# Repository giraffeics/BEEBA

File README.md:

# BEEBA

An 8-bit computer built using 7400 Series discrete logic chips.

## Repository Layout

The "CAD" folder contains all design files for the printed circuit boards. These are KiCAD documents.
The "Assembler" folder contains the C++ source code for the assembler, as well as the list of register names and some programs written in BEEBA assembly language. The assembler can be compiled with MinGW on Windows, and has not been tested on other compilers or operating systems.

## Assembly Language

Assembly language programs can be in any plain-text file format. The language is not case-sensitive. Each instruction copies eight bits of data from one register location to another. A line of code can follow one of three formats:

### COPY [read location] TO [write location]

Reads one byte of data from the register specified by [read location], writes data to the register specified by [write location].

### SET [write location] TO [data]

Writes a byte of data specified by [data] to the register specified by [write location]. [data] can be a two-digit hexadecimal number or a marker.

### MARK [marker name]

Marks the instruction position that corresponds to the following line of code. This does not represent an actual instruction. [marker name] can be referenced by SET instructions before or after the location of the marker, using a colon to specify which byte of the marker's location to use. This ranges from 0 (least significant) to 2 (most significant).

For all of these, any text after the last parameter will be ignored. However, it must be separated by a space or tab from the last parameter.

Register names are listed in REGISTER_NAMES.txt. The assembler uses this file to convert names to addresses while compiling programs.

## Using The Assembler

To use the assembler, simply drag assembly source files onto the compiled executable.

As BEEBA uses two physical ROM chips to store 16-bit-wide instructions, the assembler will output two .bin files. One of these is loaded onto the ROM chip on the left, the other is loaded onto the ROM chip on the right. They are named accordingly.

## Known Issues

When writing a constant to a register, the value will be corrupted unless the same data is sent to another register in the next instruction. The current workaround is to send data to NULL, which is an unused register.

The NES controller interface board cannot read the state of the A button. Pannenkoek2012 would love this.

The "Basic IO Board"'s input does not work at all. This was caused by oversights during the transition from TTL to CMOS. Output is still fully functional.

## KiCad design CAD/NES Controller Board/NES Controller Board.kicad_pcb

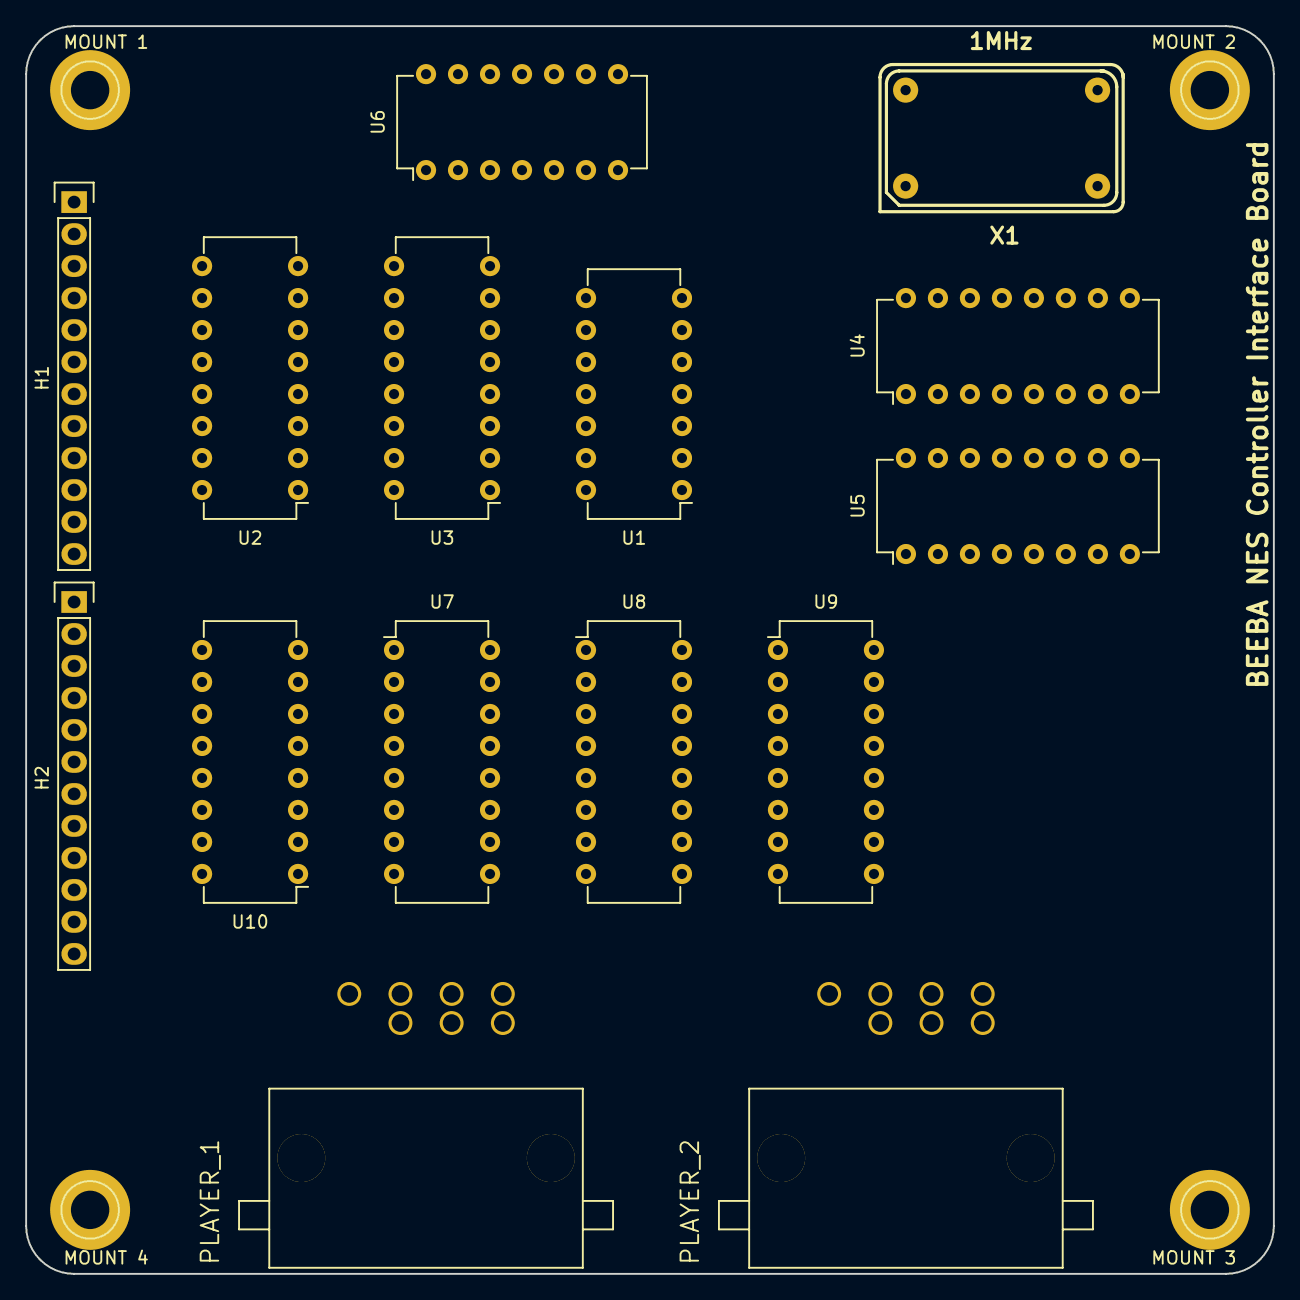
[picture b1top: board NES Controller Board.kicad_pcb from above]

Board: 2 copper layers, 99.1 x 99.1 mm, 19 parts (0 on the bottom side), 42 nets, no tracks yet.

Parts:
H1, H2: CONN_01X12; Socket_Strip_Straight_1x12
MOUNT 1, MOUNT 2, MOUNT 3, MOUNT 4: 1pin
PLAYER_1, PLAYER_2: NES_Controller_Port; NES_Controller_Port_RA
U1: 74LS04; DIP-14_W7.62mm
U2, U3: 74LS595; DIP-16_W7.62mm
U4, U7, U8: 74LS193; DIP-16_W7.62mm
U5, U9: 74LS85; DIP-16_W7.62mm
U6: 74LS08; DIP-14_W7.62mm
U10: 74LS138; DIP-16_W7.62mm
X1: 1MHz; XO-14S

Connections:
CNT0: U1.1, U6.2, U7.3, U9.10
CNT1: U1.5, U7.2, U9.12
CNT2: U7.6, U9.13
CNT4: U1.3, U6.9, U8.3, U9.15
DATA0: H1.10, U2.15, U3.15
DATA1: H1.9, U2.1, U3.1
DATA2: H1.8, U2.2, U3.2
DATA3: H1.7, U2.3, U3.3
DATA4: H1.6, U2.4, U3.4
DATA5: H1.5, U2.5, U3.5
DATA6: H1.4, U2.6, U3.6
DATA7: H1.3, U2.7, U3.7
GND: PLAYER_1.1, PLAYER_2.1, U1.7, U2.8, U3.8, U4.8, U5.2, U5.4, U5.8, U5.10, U5.15, U6.7, U7.8, U8.8, U9.2, U9.4, U9.8, U9.14, U10.8, X1.7
LATCH: PLAYER_1.3, PLAYER_2.3, U2.12, U3.12, U6.8
NCNT4: U1.4, U6.1, U6.5
unnamed: PLAYER_1.2, PLAYER_2.2, U6.6
unnamed: U1.2, U6.4
unnamed: U1.6, U6.10
unnamed: U1.8, U10.4
unnamed: U1.10, U2.14
unnamed: U1.12, U3.14
unnamed: U2.11, U3.11, U6.3
unnamed: U4.2, U5.14
unnamed: U4.3, U5.1
unnamed: U4.5, X1.8
unnamed: U4.6, U5.11
unnamed: U4.7, U5.9
unnamed: U4.14, U5.6, U7.5
unnamed: U7.12, U8.5
unnamed: U7.13, U8.4
unnamed: U7.14, U8.14, U9.6
P1_DATA: PLAYER_1.4, U1.11
P2_DATA: PLAYER_2.4, U1.13
READ0: H2.4, U10.1
READ1: H2.3, U10.2
READ2: H2.2, U10.3
READ3: H2.1, U1.9
READ4: H1.12, U10.5
READ5: H1.11, U10.6
RS43: U2.13, U10.12
RS44: U3.13, U10.11
VCC: H1.1, PLAYER_1.7, PLAYER_2.7, U1.14, U2.10, U2.16, U3.10, U3.16, U4.4, U4.11, U4.16, U5.3, U5.12, U5.13, U5.16, U6.14, U7.4, U7.11, U7.16, U8.11, U8.16, U9.1, U9.3, U9.9, U9.11, U9.16, U10.16, X1.14

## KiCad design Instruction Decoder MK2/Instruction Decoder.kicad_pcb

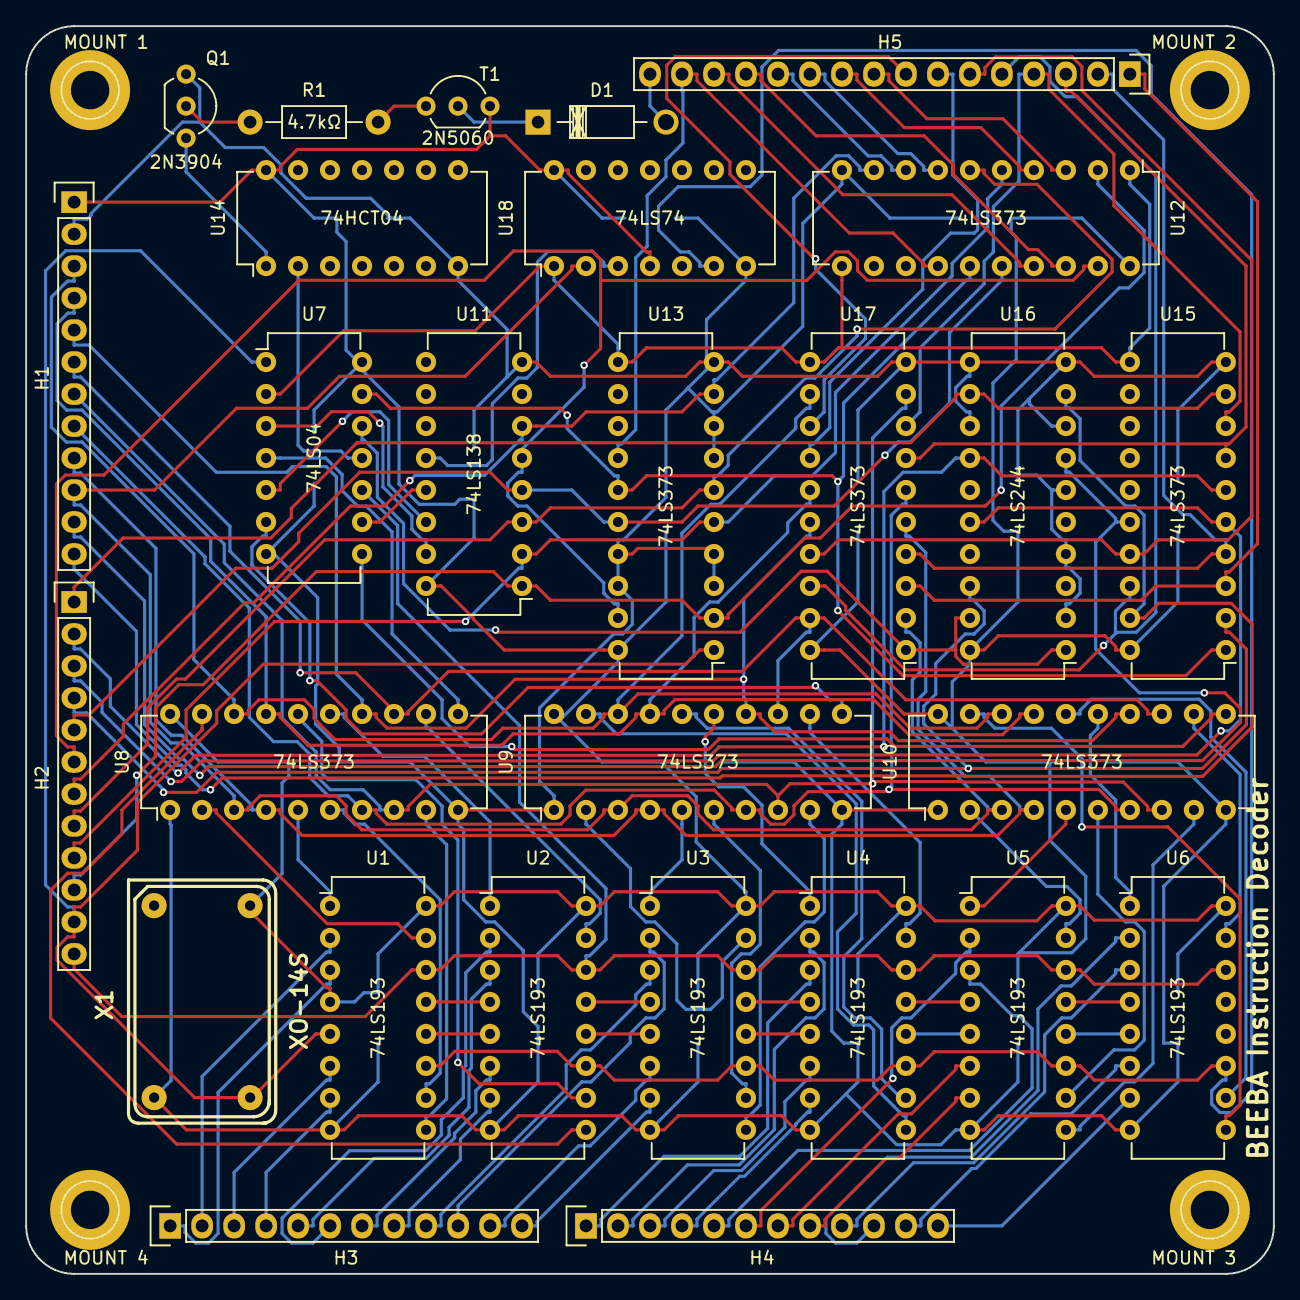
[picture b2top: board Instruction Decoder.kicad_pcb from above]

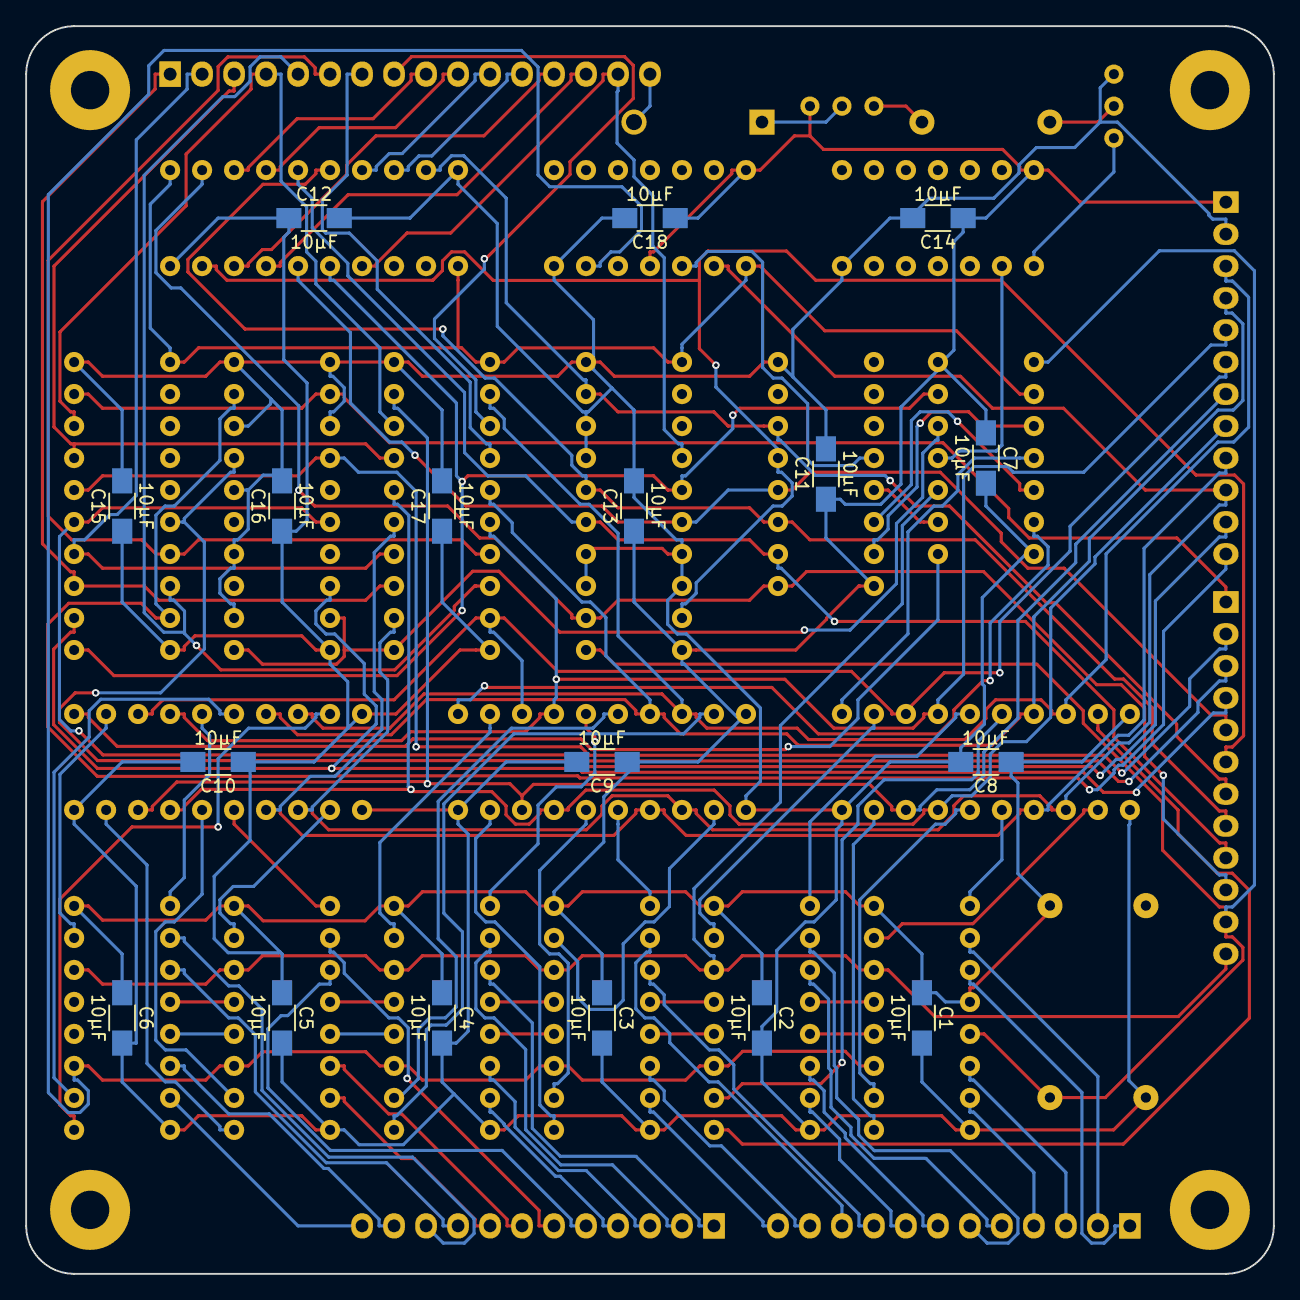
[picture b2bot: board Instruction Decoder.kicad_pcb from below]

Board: 2 copper layers, 99.1 x 99.1 mm, 50 parts (18 on the bottom side), 114 nets.

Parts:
C1, C2, C3, C4, C5, C6, C7, C8, C9, C10, C11, C12, C13, C14, C15, C16, C17, C18: 10µF; C_1206_HandSoldering
D1: D; Diode_DO-41_SOD81_Horizontal_RM10
H1, H2, H3, H4: CONN_01X12; Socket_Strip_Straight_1x12
H5: CONN_01X16; Socket_Strip_Straight_1x16
MOUNT 1, MOUNT 2, MOUNT 3, MOUNT 4: 1pin
Q1: 2N3904; TO-92_Inline_Wide
R1: 4.7kΩ; Resistor_Horizontal_RM10mm
T1: 2N5060; TO-92_Inline_Wide
U1, U2, U3, U4, U5, U6: 74LS193; DIP-16_W7.62mm
U7: 74LS04; DIP-14_W7.62mm
U8, U9, U10, U12, U13, U15, U17: 74LS373; DIP-20_W7.62mm
U11: 74LS138; DIP-16_W7.62mm
U14: 74HCT04; DIP-14_W7.62mm
U16: 74LS244; DIP-20_W7.62mm
U18: 74LS74; DIP-14_W7.62mm
X1: XO-14S

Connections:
CLOCK: H2.11, U1.5, U7.1, U13.1, X1.8
DATA0: H1.10, U8.3, U9.3, U10.3, U17.2, U18.2
DATA1: H1.9, U8.4, U9.4, U10.4, U17.5
DATA2: H1.8, U8.7, U9.7, U10.7, U17.6
DATA3: H1.7, U8.8, U9.8, U10.8, U17.9
DATA4: H1.6, U8.13, U9.13, U10.13, U17.19
DATA5: H1.5, U8.14, U9.14, U10.14, U17.16
DATA6: H1.4, U8.17, U9.17, U10.17, U17.15
DATA7: H1.3, U8.18, U9.18, U10.18, U17.12
GND: C1.2, C2.2, C3.2, C4.2, C5.2, C6.2, C7.2, C8.2, C9.2, C10.2, C11.2, C12.2, C13.2, C14.2, C15.2, C16.2, C17.2, C18.2, H1.2, Q1.1, U1.8, U2.8, U3.8, U4.8, U5.8, U6.8, U7.7, U8.1, U8.10, U9.1, U9.10, U10.1, U10.10, U11.8, U12.10, U13.3, U13.4, U13.7, U13.8, U13.10, U13.17, U13.18, U14.7, U15.10, U16.2, U16.4, U16.6, U16.8, U16.10, U16.11, U16.13, U17.10, U18.7, X1.7
II00: H5.1, U15.3, U17.3
II01: H5.2, U15.4, U17.4
II02: H5.3, U15.7, U17.7
II03: H5.4, U15.8, U17.8
II04: H5.5, U15.18, U17.18
II05: H5.6, U15.17, U17.17
II06: H5.7, U17.14
II07: H5.8, U17.13
II08: H5.9, U12.3
II09: H5.10, U12.4
II10: H5.11, U12.7
II11: H5.12, U12.8
II12: H5.13, U12.18
II13: H5.14, U12.17
II14: H5.15, U12.14, U13.14
II15: D1.2, H5.16
IL14: U7.13, U12.15, U13.15, U15.1
LOADP: U1.11, U2.11, U3.11, U4.11, U5.11, U6.11, U18.6
NCLOCK: U7.2, U12.1, U12.11, U13.11, U15.11, U17.11, U18.1
unnamed: D1.1, T1.G
unnamed: Q1.2, R1.2
unnamed: Q1.3, U14.1
unnamed: R1.1, T1.K
unnamed: U1.12, U2.5
unnamed: U1.13, U2.4
unnamed: U2.12, U3.5
unnamed: U2.13, U3.4
unnamed: U3.12, U4.5
unnamed: U3.13, U4.4
unnamed: U5.12, U6.5
unnamed: U5.13, U6.4
unnamed: U7.4, U8.11
unnamed: U7.6, U9.11
unnamed: U7.8, U10.11
unnamed: U7.11, U14.2
unnamed: U7.12, U16.1, U16.19, U17.1
PI00: U1.15, U8.2
PI01: U1.1, U8.5
PI02: U1.10, U8.6
PI03: U1.9, U8.9
PI04: U2.15, U8.12
PI05: U2.1, U8.15
PI06: U2.10, U8.16
PI07: U2.9, U8.19
PI08: U3.15, U9.2
PI09: U3.1, U9.5
PI10: U3.10, U9.6
PI11: U3.9, U9.9
PI12: U4.15, U9.12
PI13: U4.1, U9.15
PI14: U4.10, U9.16
PI15: U4.9, U9.19
PI16: U5.15, U10.2
PI17: U5.1, U10.5
PI18: U5.10, U10.6
PI19: U5.9, U10.9
PI20: U6.15, U10.12
PI21: U6.1, U10.15
PI22: U6.10, U10.16
PI23: U6.9, U10.19
PO00: H3.1, U1.3
PO01: H3.2, U1.2
PO02: H3.3, U1.6
PO03: H3.4, U1.7
PO04: H3.5, U2.3
PO05: H3.6, U2.2
PO06: H3.7, U2.6
PO07: H3.8, U2.7
PO08: H3.9, U3.3
PO09: H3.10, U3.2
PO10: H3.11, U3.6
PO11: H3.12, U3.7
PO12: H4.1, U4.3
PO13: H4.2, U4.2
PO14: H4.3, U4.6
PO15: H4.4, U4.7
PO16: H4.5, U5.3
PO17: H4.6, U5.2
PO18: H4.7, U5.6
PO19: H4.8, U5.7
PO20: H4.9, U6.3
PO21: H4.10, U6.2
PO22: H4.11, U6.6
PO23: H4.12, U6.7
READ0: H2.4, U15.2, U16.18
READ1: H2.3, U15.5, U16.16
READ2: H2.2, U15.6, U16.14
READ3: H2.1, U15.9, U16.12
READ4: H1.12, U15.19, U16.9
READ5: H1.11, U15.16, U16.7
RESET: H2.12, U1.14, U2.14, U3.14, U4.14, U5.14, U6.14, U7.10
TC1: U4.12, U5.5
TC2: U4.13, U5.4
VCC: C1.1, C2.1, C3.1, C4.1, C5.1, C6.1, C7.1, C8.1, C9.1, C10.1, C11.1, C12.1, C13.1, C14.1, C15.1, C16.1, C17.1, C18.1, H1.1, T1.A, U1.4, U1.16, U2.16, U3.16, U4.16, U5.16, U6.16, U7.14, U8.20, U9.20, U10.20, U11.16, U12.20, U13.20, U14.14, U15.20, U16.20, U17.20, U18.4, U18.14, X1.14
WRITE0: H2.10, U11.1, U12.2, U13.2
WRITE1: H2.9, U11.2, U12.5, U13.5
WRITE2: H2.8, U11.3, U12.6, U13.6
WRITE3: H2.7, U11.6, U12.9, U13.9
WRITE4: H2.6, U11.5, U12.19, U13.19
WRITE5: H2.5, U11.4, U12.16, U13.16
WS08: U7.3, U11.15
WS09: U7.5, U11.14
WS10: U7.9, U11.13
WS11: U11.12, U18.3

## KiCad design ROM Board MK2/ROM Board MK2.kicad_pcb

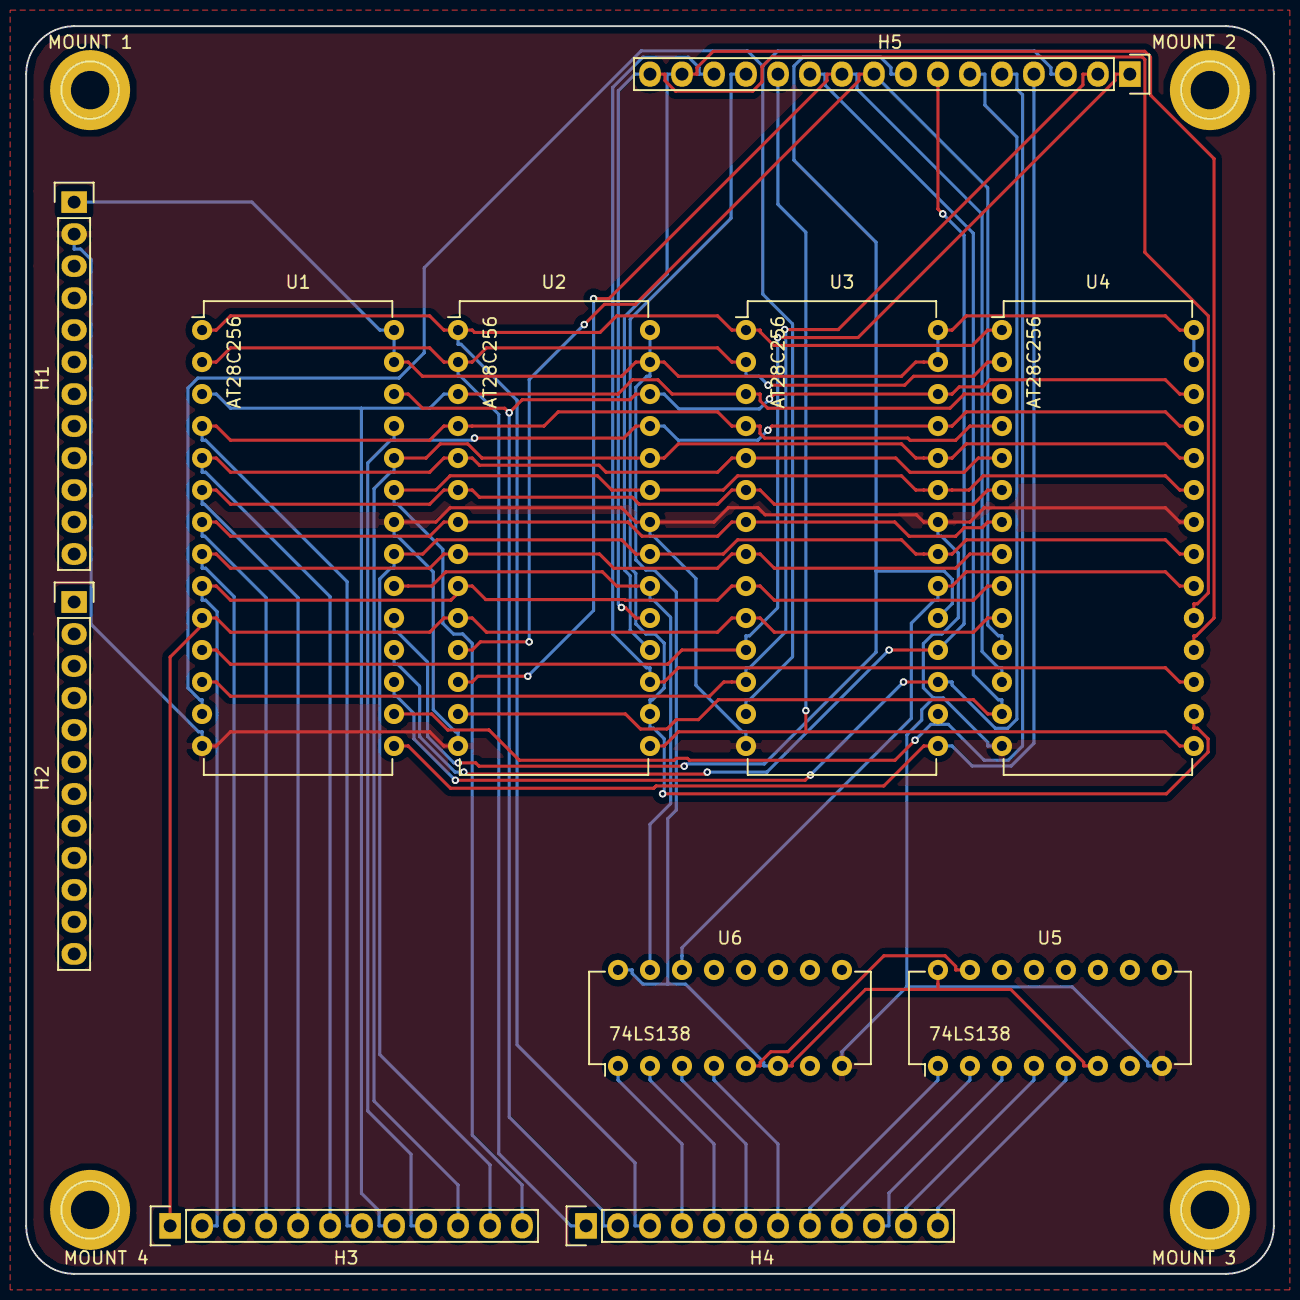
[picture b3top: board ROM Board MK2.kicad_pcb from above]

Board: 2 copper layers, 99.1 x 99.1 mm, 15 parts (0 on the bottom side), 45 nets.

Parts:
H1, H2, H3, H4: CONN_01X12; Socket_Strip_Straight_1x12
H5: CONN_01X16; Socket_Strip_Straight_1x16
MOUNT 1, MOUNT 2, MOUNT 3, MOUNT 4: 1pin
U1, U2, U3, U4: AT28C256; DIP-28_W15.24mm
U5, U6: 74LS138; DIP-16_W7.62mm

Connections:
GND: H1.2, U1.14, U1.22, U2.14, U2.22, U3.14, U3.22, U4.14, U4.22, U5.8, U6.8
II00: H5.1, U1.11, U3.11
II01: H5.2, U1.12, U3.12
II02: H5.3, U1.13, U3.13
II03: H5.4, U1.15, U3.15
II04: H5.5, U1.16, U3.16
II05: H5.6, U1.17, U3.17
II06: H5.7, U1.18, U3.18
II07: H5.8, U1.19, U3.19
II08: H5.9, U2.11, U4.11
II09: H5.10, U2.12, U4.12
II10: H5.11, U2.13, U4.13
II11: H5.12, U2.15, U4.15
II12: H5.13, U2.16, U4.16
II13: H5.14, U2.17, U4.17
II14: H5.15, U2.18, U4.18
II15: H5.16, U2.19, U4.19
unnamed: U5.15, U6.5
OE0: U1.20, U2.20, U6.15
OE1: U3.20, U4.20, U6.14
PO00: H3.1, U1.10, U2.10, U3.10, U4.10
PO01: H3.2, U1.9, U2.9, U3.9, U4.9
PO02: H3.3, U1.8, U2.8, U3.8, U4.8
PO03: H3.4, U1.7, U2.7, U3.7, U4.7
PO04: H3.5, U1.6, U2.6, U3.6, U4.6
PO05: H3.6, U1.5, U2.5, U3.5, U4.5
PO06: H3.7, U1.4, U2.4, U3.4, U4.4
PO07: H3.8, U1.3, U2.3, U3.3, U4.3
PO08: H3.9, U1.25, U2.25, U3.25, U4.25
PO09: H3.10, U1.24, U2.24, U3.24, U4.24
PO10: H3.11, U1.21, U2.21, U3.21, U4.21
PO11: H3.12, U1.23, U2.23, U3.23, U4.23
PO12: H4.1, U1.2, U2.2, U3.2, U4.2
PO13: H4.2, U1.26, U2.26, U3.26, U4.26
PO14: H4.3, U1.1, U2.1, U3.1, U4.1
PO15: H4.4, U6.1
PO16: H4.5, U6.2
PO17: H4.6, U6.3
PO18: H4.7, U6.4
PO19: H4.8, U5.1
PO20: H4.9, U5.2
PO21: H4.10, U5.3
PO22: H4.11, U5.4
PO23: H4.12, U5.5
VCC: H1.1, U1.27, U1.28, U2.27, U2.28, U3.27, U3.28, U4.27, U4.28, U5.6, U5.16, U6.6, U6.16

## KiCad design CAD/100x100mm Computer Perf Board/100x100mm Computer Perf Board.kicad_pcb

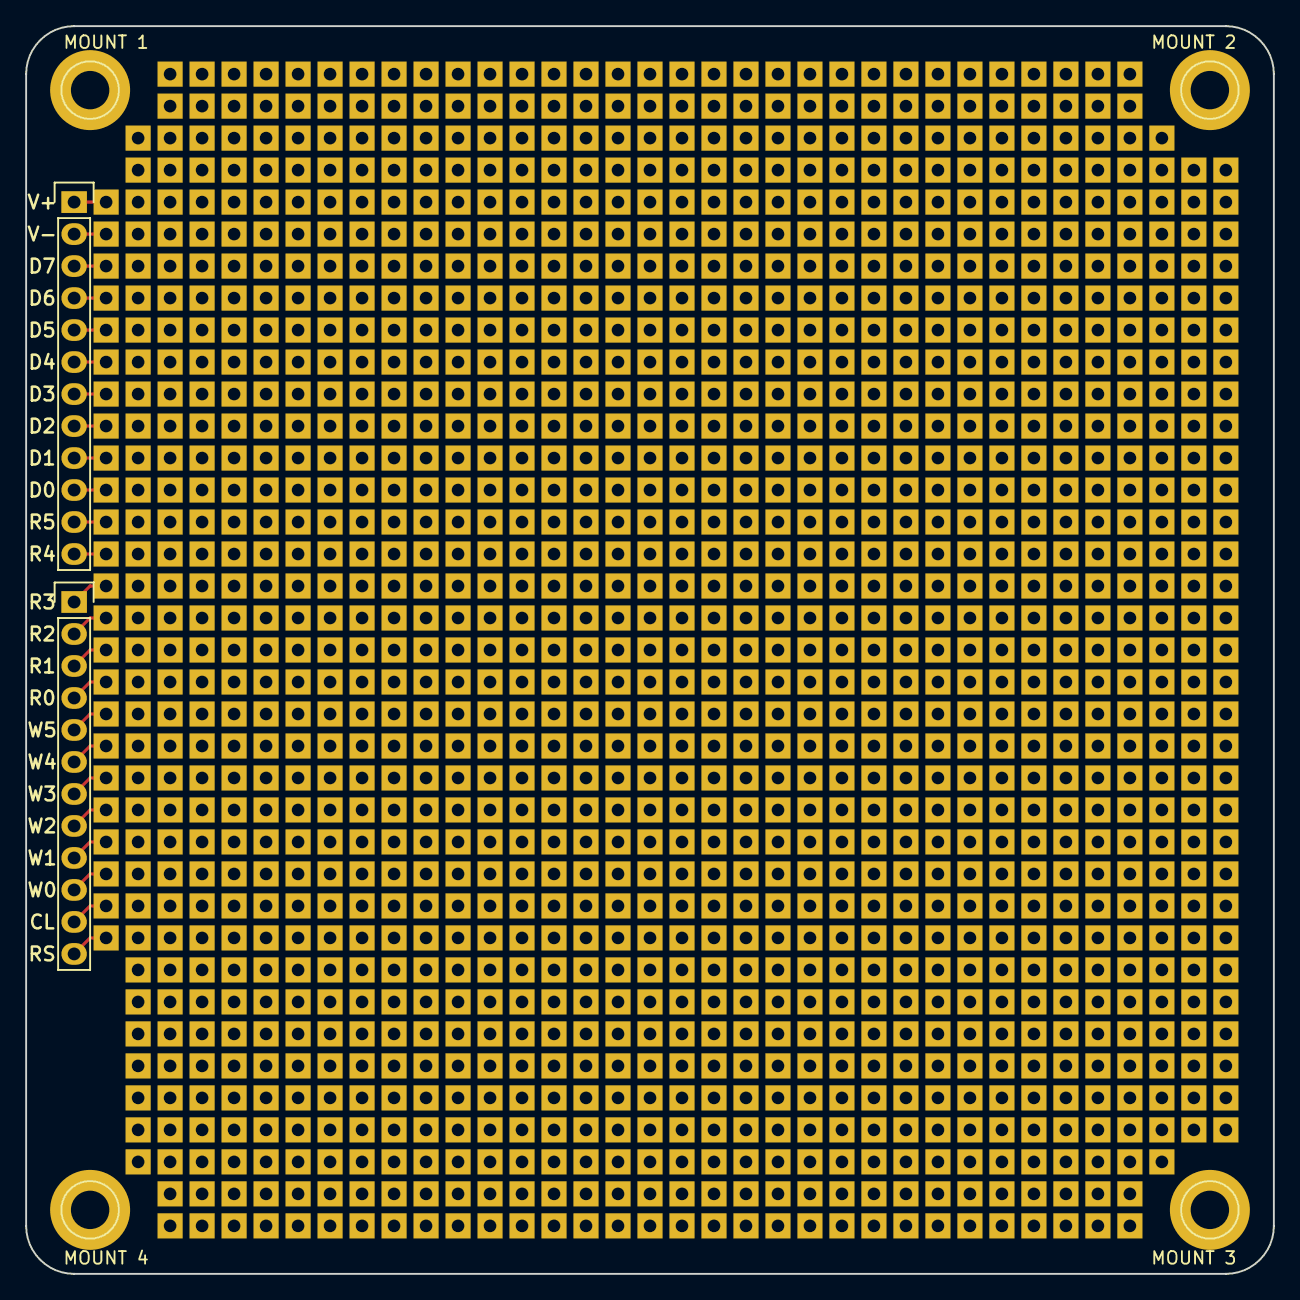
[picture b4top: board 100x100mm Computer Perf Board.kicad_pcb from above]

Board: 2 copper layers, 99.1 x 99.1 mm, 1283 parts (0 on the bottom side), 24 nets.

Parts:
111, 112, 113, 114, 115, 116, 117, 118, 119, 121, 122, 123, 124, 125, 126, 127, 128, 129, 131, 132, 133, 134, 135, 136, 137, 138, 139, 141, 142, 143, 144, 145, 146, 147, 148, 149, 151, 152, 153, 154, 155, 156, 157, 158, 159, 161, 162, 163, 164, 165, 166, 167, 168, 169, 171, 172, 173, 174, 175, 176, 177, 178, 179, 181, 182, 183, 184, 185, 186, 187, 188, 189, 191, 192, 193, 194, 195, 196, 197, 198, 199, 1101, 1102, 1103, 1104, 1105, 1106, 1107, 1108, 1109, 1110, 1111, 1111#2, 1111#3, 1112, 1112#2, 1112#3, 1113, 1113#2, 1113#3, 1114, 1114#2, 1114#3, 1115, 1115#2, 1115#3, 1116, 1116#2, 1116#3, 1117, 1117#2, 1117#3, 1118, 1118#2, 1118#3, 1119, 1119#2, 1119#3, 1120, 1121, 1121#2, 1122, 1122#2, 1123, 1123#2, 1124, 1124#2, 1125, 1125#2, 1126, 1126#2, 1127, 1127#2, 1128, 1128#2, 1129, 1129#2, 1130, 1131, 1131#2, 1132, 1132#2, 1133, 1133#2, 1134, 1134#2, 1135, 1135#2, 1136, 1136#2, 1137, 1137#2, 1138, 1139, 1141, 1142, 1143, 1144, 1145, 1146, 1147, 1148, 1149, 1151, 1152, 1153, 1154, 1155, 1156, 1157, 1158, 1159, 1161, 1162, 1163, 1164, 1165, 1166, 1167, 1168, 1169, 1171, 1172, 1173, 1174, 1175, 1176, 1177, 1178, 1179, 1181, 1182, 1183, 1184, 1185, 1186, 1187, 1188, 1189, 1191, 1192, 1193, 1194, 1195, 1196, 1197, 1198, 1199, 1201, 1202, 1203, 1204, 1205, 1206, 1207, 1208, 1209, 1210, 1211, 1211#2, 1212, 1212#2, 1213, 1213#2, 1214, 1214#2, 1215, 1215#2, 1216, 1216#2, 1217, 1217#2, 1218, 1218#2, 1219, 1219#2, 1220, 1221, 1221#2, 1222, 1222#2, 1223, 1223#2, 1224, 1224#2, 1225, 1225#2, 1226, 1226#2, 1227, 1227#2, 1228, 1228#2, 1229, 1229#2, 1230, 1231, 1231#2, 1232, 1232#2, 1233, 1233#2, 1234, 1234#2, 1235, 1235#2, 1236, 1236#2, 1237, 1237#2, 1238, 1239, 1241, 1242, 1243, 1244, 1245, 1246, 1247, 1248, 1249, 1251, 1252, 1253, 1254, 1255, 1256, 1257, 1258, 1259, 1261, 1262, 1263, 1264, 1265, 1266, 1267, 1268, 1269, 1271, 1272, 1273, 1274, 1275, 1276, 1277, 1278, 1279, 1281, 1282, 1283, 1284, 1285, 1286, 1287, 1288, 1289, 1291, 1292, 1293, 1294, 1295, 1296, 1297, 1298, 1299, 1301, 1302, 1303, 1304, 1305, 1306, 1307, 1308, 1309, 1310, 1311, 1311#2, 1312, 1312#2, 1313, 1313#2, 1314, 1314#2, 1315, 1315#2, 1316, 1316#2, 1317, 1317#2, 1318, 1318#2, 1319, 1319#2, 1320, 1321, 1322, 1323, 1324, 1325, 1326, 1327, 1328, 1329, 1330, 1331, 1332, 1333, 1334, 1335, 1336, 1337, 1410, 1411, 1412, 1413, 1414, 1415, 1416, 1417, 1418, 1419, 1420, 1421, 1422, 1423, 1424, 1425, 1426, 1427, 1428, 1429, 1430, 1431, 1432, 1433, 1434, 1435, 1436, 1437, 1510, 1511, 1512, 1513, 1514, 1515, 1516, 1517, 1518, 1519, 1520, 1521, 1522, 1523, 1524, 1525, 1526, 1527, 1528, 1529, 1530, 1531, 1532, 1533, 1534, 1535, 1536, 1537, 1610, 1611, 1612, 1613, 1614, 1615, 1616, 1617, 1618, 1619, 1620, 1621, 1622, 1623, 1624, 1625, 1626, 1627, 1628, 1629, 1630, 1631, 1632, 1633, 1634, 1635, 1636, 1637, 1710, 1711, 1712, 1713, 1714, 1715, 1716, 1717, 1718, 1719, 1720, 1721, 1722, 1723, 1724, 1725, 1726, 1727, 1728, 1729, 1730, 1731, 1732, 1733, 1734, 1735, 1736, 1737, 1810, 1811, 1812, 1813, 1814, 1815, 1816, 1817, 1818, 1819, 1820, 1821, 1822, 1823, 1824, 1825, 1826, 1827, 1828, 1829, 1830, 1831, 1832, 1833, 1834, 1835, 1836, 1837, 1910, 1911, 1912, 1913, 1914, 1915, 1916, 1917, 1918, 1919, 1920, 1921, 1922, 1923, 1924, 1925, 1926, 1927, 1928, 1929, 1930, 1931, 1932, 1933, 1934, 1935, 1936, 1937, 11010, 11011, 11012, 11013, 11014, 11015, 11016, 11017, 11018, 11019, 11020, 11021, 11022, 11023, 11024, 11025, 11026, 11027, 11028, 11029, 11030, 11031, 11032, 11033, 11034, 11035, 11036, 11037, 11110, 11110#2, 11111, 11111#2, 11112, 11112#2, 11113, 11113#2, 11114, 11114#2, 11115, 11115#2, 11116, 11116#2, 11117, 11117#2, 11118, 11118#2, 11119, 11119#2, 11120, 11120#2, 11121, 11121#2, 11122, 11122#2, 11123, 11123#2, 11124, 11124#2, 11125, 11125#2, 11126, 11126#2, 11127, 11127#2, 11128, 11128#2, 11129, 11129#2, 11130, 11130#2, 11131, 11131#2, 11132, 11132#2, 11133, 11133#2, 11134, 11135, 11136, 11137, 11210, 11211, 11212, 11213, 11214, 11215, 11216, 11217, 11218, 11219, 11220, 11221, 11222, 11223, 11224, 11225, 11226, 11227, 11228, 11229, 11230, 11231, 11232, 11233, 11234, 11235, 11236, 11237, 11310, 11311, 11312, 11313, 11314, 11315, 11316, 11317, 11318, 11319, 11320, 11321, 11322, 11323, 11324, 11325, 11326, 11327, 11328, 11329, 11330, 11331, 11332, 11333, 11334, 11335, 11336, 11337, 11410, 11411, 11412, 11413, 11414, 11415, 11416, 11417, 11418, 11419, 11420, 11421, 11422, 11423, 11424, 11425, 11426, 11427, 11428, 11429, 11430, 11431, 11432, 11433, 11434, 11435, 11436, 11437, 11510, 11511, 11512, 11513, 11514, 11515, 11516, 11517, 11518, 11519, 11520, 11521, 11522, 11523, 11524, 11525, 11526, 11527, 11528, 11529, 11530, 11531, 11532, 11533, 11534, 11535, 11536, 11537, 11610, 11611, 11612, 11613, 11614, 11615, 11616, 11617, 11618, 11619, 11620, 11621, 11622, 11623, 11624, 11625, 11626, 11627, 11628, 11629, 11630, 11631, 11632, 11633, 11634, 11635, 11636, 11637, 11710, 11711, 11712, 11713, 11714, 11715, 11716, 11717, 11718, 11719, 11720, 11721, 11722, 11723, 11724, 11725, 11726, 11727, 11728, 11729, 11730, 11731, 11732, 11733, 11734, 11735, 11736, 11737, 11810, 11811, 11812, 11813, 11814, 11815, 11816, 11817, 11818, 11819, 11820, 11821, 11822, 11823, 11824, 11825, 11826, 11827, 11828, 11829, 11830, 11831, 11832, 11833, 11834, 11835, 11836, 11837, 11910, 11911, 11912, 11913, 11914, 11915, 11916, 11917, 11918, 11919, 11920, 11921, 11922, 11923, 11924, 11925, 11926, 11927, 11928, 11929, 11930, 11931, 11932, 11933, 11934, 11935, 11936, 11937, 12010, 12011, 12012, 12013, 12014, 12015, 12016, 12017, 12018, 12019, 12020, 12021, 12022, 12023, 12024, 12025, 12026, 12027, 12028, 12029, 12030, 12031, 12032, 12033, 12034, 12035, 12036, 12037, 12110, 12111, 12112, 12113, 12114, 12115, 12116, 12117, 12118, 12119, 12120, 12121, 12122, 12123, 12124, 12125, 12126, 12127, 12128, 12129, 12130, 12131, 12132, 12133, 12134, 12135, 12136, 12137, 12210, 12211, 12212, 12213, 12214, 12215, 12216, 12217, 12218, 12219, 12220, 12221, 12222, 12223, 12224, 12225, 12226, 12227, 12228, 12229, 12230, 12231, 12232, 12233, 12234, 12235, 12236, 12237, 12310, 12311, 12312, 12313, 12314, 12315, 12316, 12317, 12318, 12319, 12320, 12321, 12322, 12323, 12324, 12325, 12326, 12327, 12328, 12329, 12330, 12331, 12332, 12333, 12334, 12335, 12336, 12337, 12410, 12411, 12412, 12413, 12414, 12415, 12416, 12417, 12418, 12419, 12420, 12421, 12422, 12423, 12424, 12425, 12426, 12427, 12428, 12429, 12430, 12431, 12432, 12433, 12434, 12435, 12436, 12437, 12510, 12511, 12512, 12513, 12514, 12515, 12516, 12517, 12518, 12519, 12520, 12521, 12522, 12523, 12524, 12525, 12526, 12527, 12528, 12529, 12530, 12531, 12532, 12533, 12534, 12535, 12536, 12537, 12610, 12611, 12612, 12613, 12614, 12615, 12616, 12617, 12618, 12619, 12620, 12621, 12622, 12623, 12624, 12625, 12626, 12627, 12628, 12629, 12630, 12631, 12632, 12633, 12634, 12635, 12636, 12637, 12710, 12711, 12712, 12713, 12714, 12715, 12716, 12717, 12718, 12719, 12720, 12721, 12722, 12723, 12724, 12725, 12726, 12727, 12728, 12729, 12730, 12731, 12732, 12733, 12734, 12735, 12736, 12737, 12810, 12811, 12812, 12813, 12814, 12815, 12816, 12817, 12818, 12819, 12820, 12821, 12822, 12823, 12824, 12825, 12826, 12827, 12828, 12829, 12830, 12831, 12832, 12833, 12834, 12835, 12836, 12837, 12910, 12911, 12912, 12913, 12914, 12915, 12916, 12917, 12918, 12919, 12920, 12921, 12922, 12923, 12924, 12925, 12926, 12927, 12928, 12929, 12930, 12931, 12932, 12933, 12934, 12935, 12936, 12937, 13010, 13011, 13012, 13013, 13014, 13015, 13016, 13017, 13018, 13019, 13020, 13021, 13022, 13023, 13024, 13025, 13026, 13027, 13028, 13029, 13030, 13031, 13032, 13033, 13034, 13035, 13036, 13037, 13110, 13111, 13111#2, 13112, 13112#2, 13113, 13113#2, 13114, 13114#2, 13115, 13115#2, 13116, 13116#2, 13117, 13117#2, 13118, 13118#2, 13119, 13119#2, 13120, 13121, 13122, 13123, 13124, 13125, 13126, 13127, 13128, 13129, 13130, 13131, 13132, 13133, 13134, 13135, 13136, 13137, 131110, 131111, 131111#2, 131112, 131112#2, 131113, 131113#2, 131114, 131114#2, 131115, 131115#2, 131116, 131116#2, 131117, 131117#2, 131118, 131118#2, 131119, 131119#2, 131120, 131121, 131121#2, 131122, 131122#2, 131123, 131123#2, 131124, 131124#2, 131125, 131125#2, 131126, 131126#2, 131127, 131127#2, 131128, 131128#2, 131129, 131129#2, 131130, 131131, 131132, 131133, 1311110, 1311111, 1311112, 1311113, 1311114, 1311115, 1311116, 1311117, 1311118, 1311119, 1311120, 1311121, 1311122, 1311123, 1311124, 1311125, 1311126, 1311127, 1311128, 1311129, 1311130, 1311131, 1311210, 1311211, 1311212, 1311213, 1311214, 1311215, 1311216, 1311217, 1311218, 1311219, 1311220, 1311221, 1311222, 1311223, 1311224, 1311225, 1311226, 1311227, 1311228, 1311229, 1311230, 1311231: 1pin
H1, H2: CONN_01X12; Socket_Strip_Straight_1x12
H3, H4: CONN_01X12; 12pin_square_nodecor
MOUNT 1, MOUNT 2, MOUNT 3, MOUNT 4: 1pin

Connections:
DATA0: H1.10, H3.10
DATA1: H1.9, H3.9
DATA2: H1.8, H3.8
DATA3: H1.7, H3.7
DATA4: H1.6, H3.6
DATA5: H1.5, H3.5
DATA6: H1.4, H3.4
DATA7: H1.3, H3.3
GND: H1.2, H3.2
unnamed: H2.11, H4.11
unnamed: H2.12, H4.12
READ0: H2.4, H4.4
READ1: H2.3, H4.3
READ2: H2.2, H4.2
READ3: H2.1, H4.1
READ4: H1.12, H3.12
READ5: H1.11, H3.11
VCC: H1.1, H3.1
WRITE0: H2.10, H4.10
WRITE1: H2.9, H4.9
WRITE2: H2.8, H4.8
WRITE3: H2.7, H4.7
WRITE4: H2.6, H4.6
WRITE5: H2.5, H4.5
